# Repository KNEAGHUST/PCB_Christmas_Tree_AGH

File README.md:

<h2>🧐 Features</h2>

So... it's a christmas tree... just made from a PCB!

It is green, has stars on it and... it blinks!

<h2>💾 PCB Design</h2>

The schematics and PCB were designed using KiCAD 7. All the files are available in this repository.

The christmass tree is actually made up of two PCB, that slide into each other and you can solder them toghether.

<h2>💻 Built with</h2>

Technologies used in the project:

*  Microchips Attiny402 microcontroller
*  0805 LEDs and resistors
*  CR2032 battery
*  6 mm tact switch for changing blink modes

<h2>📖 Documentation and project files </h2>

The CTree submodule contains all the code for the attiny, feel free to create pull requests with your own improvements!

KiCAD files has all the schematics and pcb files you might need, but if you just want to build one without making any changes,
Manufacturing files folder has all the gerber files you will need.

Under Materials you should find the current BOM and any oher useful files.

UPDIProgrammer is a python script used to flash the Attiny microcontrolller.

<h2>🛡️ License:</h2>

This project is licensed under the MIT License.

<h2> 🙋‍♂️Authors </h2>

- Krzysztof Sikora (hardware)
- Marek Pawłowski (firmware)

<h2>💖Like my work?</h2>

If you have any questions about the project feel free to contact us via email: krzysieksikora717@gmail.com

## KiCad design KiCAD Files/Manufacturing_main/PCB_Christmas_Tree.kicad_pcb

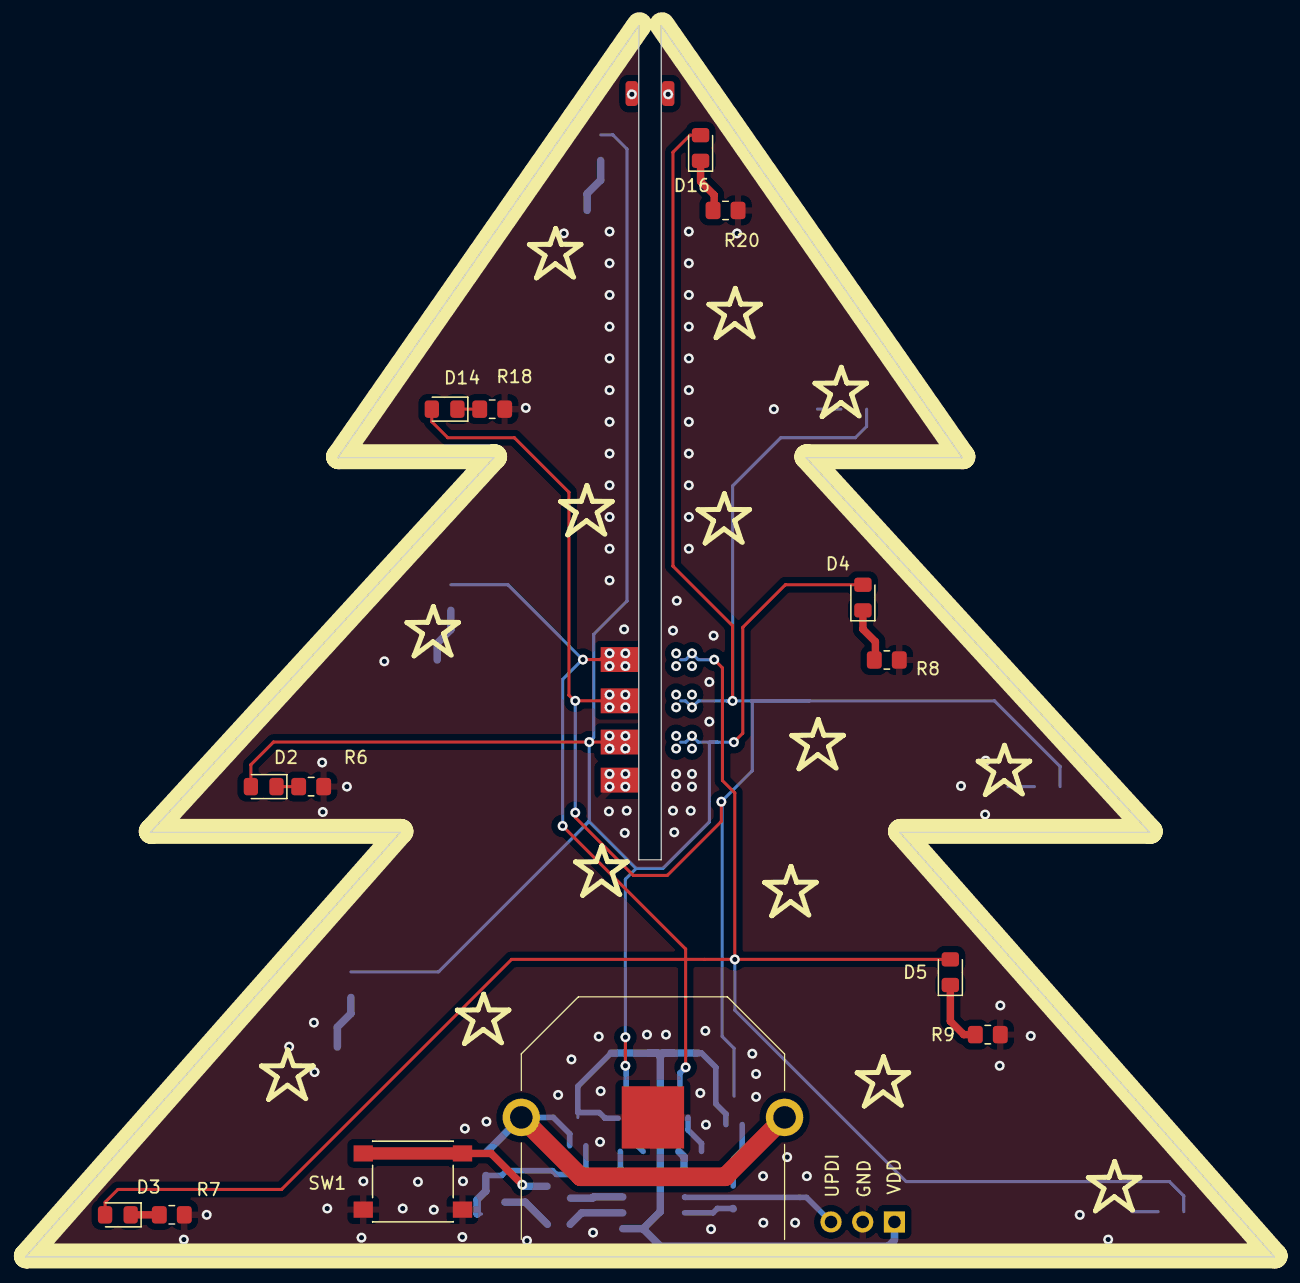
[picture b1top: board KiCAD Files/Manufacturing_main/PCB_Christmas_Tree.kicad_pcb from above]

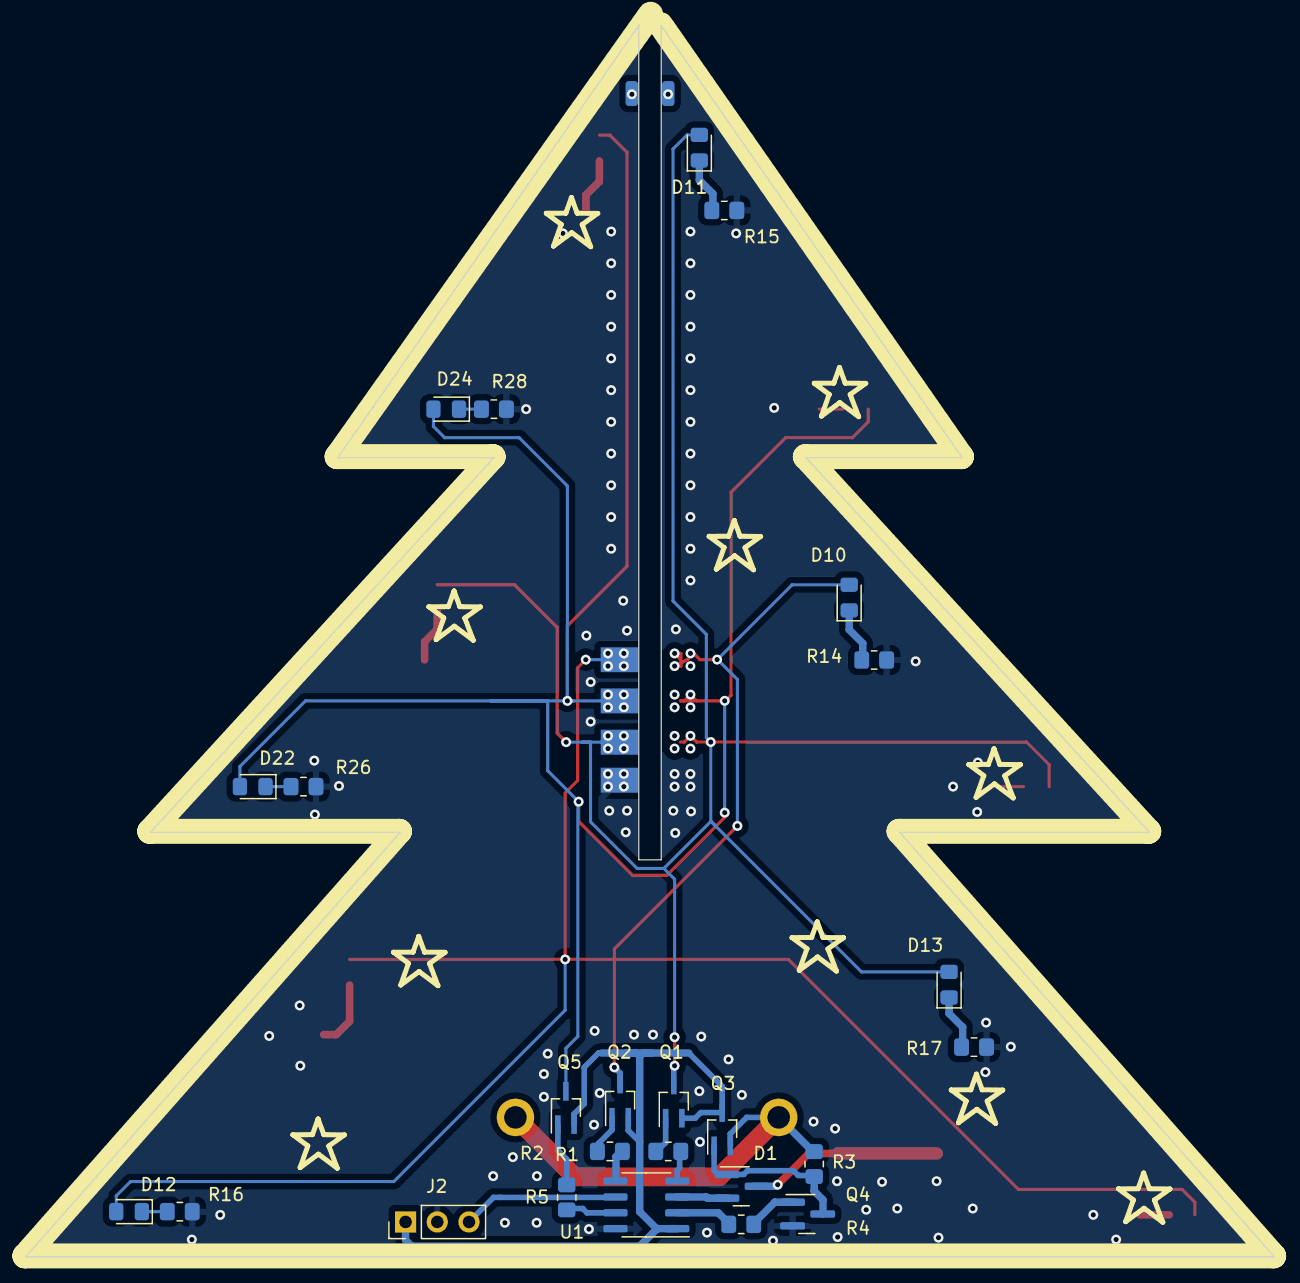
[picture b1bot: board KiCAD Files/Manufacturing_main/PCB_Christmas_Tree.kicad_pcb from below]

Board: 2 copper layers, 100.0 x 98.6 mm, 41 parts (26 on the bottom side), 21 nets.

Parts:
D1: D_Schottky_Dual_CommonCathode_AAK; SOT-23
D2, D3, D4, D5, D10, D11, D12, D13, D14, D16, D22, D24: LED; LED_0805_2012Metric_Pad1.15x1.40mm_HandSolder
J1: CR2032; BC-2002
J2: Conn_01x03_Pin; PinHeader_1x03_P2.54mm_Vertical
J3, J6: Conn_01x04_Pin; Multi_board_connector
Q1, Q2, Q3, Q5: AO3401A; SOT-323_SC-70_Handsoldering
Q4: BC817; SOT-23
R1, R2, R3, R4, R5: 10k; R_0805_2012Metric_Pad1.20x1.40mm_HandSolder
R6, R7, R8, R9, R14, R15, R16, R17, R18, R20, R26, R28: 100; R_0805_2012Metric_Pad1.20x1.40mm_HandSolder
SW1: SW_Omron_B3FS; SW_Push_1P1T_NO_6x6mm_H9.5mm
U1: ATtiny402-SS; SOIC-8_3.9x4.9mm_P1.27mm

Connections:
+BATT: J1.1, Q3.2 (S), R3.1
/LED_Power_1: D3.2 (A), D5.2 (A), D10.2 (A), D12.2 (A), J3.1, J6.1, Q2.3 (D)
/LED_Power_2: D14.2 (A), D16.2 (A), D22.2 (A), D24.2 (A), J3.2, J6.2, Q5.3 (D)
/LED_Power_3: D2.2 (A), D4.2 (A), D11.2 (A), D13.2 (A), J3.3, J6.3, Q1.3 (D)
/LED_Set_1: R2.1, U1.5 (PA2)
/LED_Set_2: R5.1, U1.7 (PA3)
/LED_Set_3: R1.1, U1.4 (PA1)
/Power_sustain: R4.2, U1.2 (PA6)
/Switch_in: D1.2 (A), U1.3 (PA7)
/UDPI: J2.3, U1.6 (~RESET/PA0)
GND: J1.2, J2.2, J3.4, J6.4, Q4.2 (E), R6.2, R7.2, R8.2, R9.2, R14.2, R15.2, R16.2, R17.2, R18.2, R20.2, R26.2, R28.2, SW1.1, U1.8 (GND)
unnamed: D1.3 (K), SW1.2
unnamed: D10.1 (K), R14.1
unnamed: D12.1 (K), R16.1
unnamed: D22.1 (K), R26.1
unnamed: Q1.1 (G), R1.2
unnamed: Q2.1 (G), R2.2
unnamed: D1.1 (A), Q3.1 (G), Q4.3 (C), R3.2
unnamed: Q4.1 (B), R4.1
unnamed: Q5.1 (G), R5.2
VDD: J2.1, Q1.2 (S), Q2.2 (S), Q3.3 (D), Q5.2 (S), U1.1 (VCC)

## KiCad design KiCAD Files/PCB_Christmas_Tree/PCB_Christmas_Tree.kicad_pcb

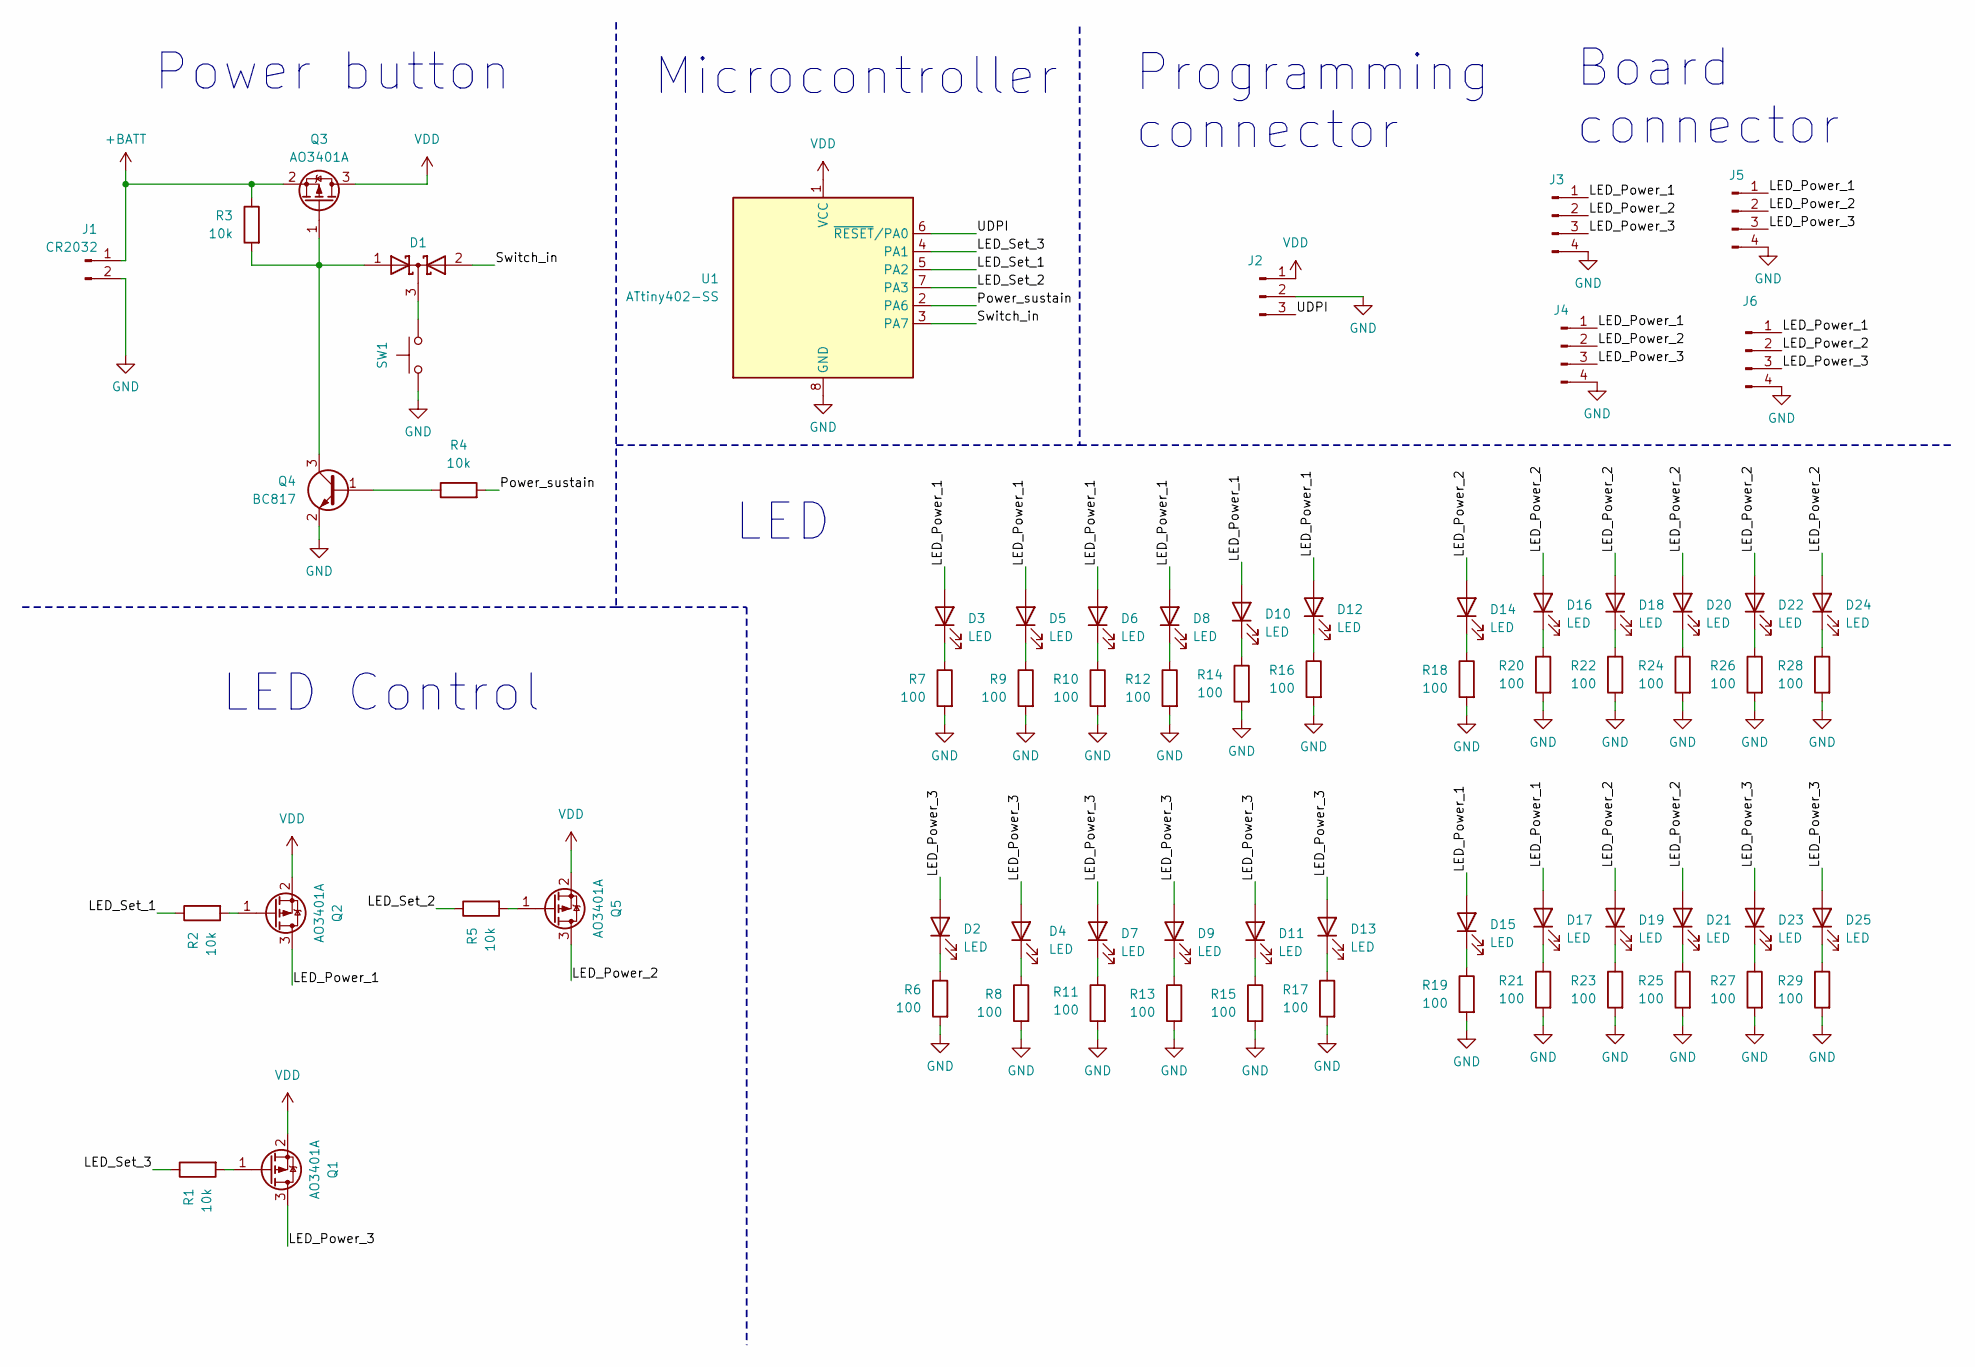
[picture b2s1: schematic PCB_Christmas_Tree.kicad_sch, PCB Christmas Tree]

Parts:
D1: D_Schottky_Dual_CommonCathode_AAK; SOT-23
D2, D3, D4, D5, D6, D7, D8, D9, D10, D11, D12, D13, D14, D15, D16, D17, D18, D19, D20, D21, D22, D23, D24, D25: LED; LED_0805_2012Metric_Pad1.15x1.40mm_HandSolder
J1: CR2032; BC-2002
J2: Conn_01x03_Pin; PinHeader_1x03_P2.54mm_Vertical
J3, J4, J5, J6: Conn_01x04_Pin; Multi_board_connector
Q1, Q2, Q3, Q5: AO3401A; SOT-323_SC-70_Handsoldering
Q4: BC817; SOT-23
R1, R2, R3, R4, R5: 10k; R_0805_2012Metric_Pad1.20x1.40mm_HandSolder
R6, R7, R8, R9, R10, R11, R12, R13, R14, R15, R16, R17, R18, R19, R20, R21, R22, R23, R24, R25, R26, R27, R28, R29: 100; R_0805_2012Metric_Pad1.20x1.40mm_HandSolder
SW1: SW_Omron_B3FS; SW_Push_1P1T_NO_6x6mm_H9.5mm
U1: ATtiny402-SS; SOIC-8_3.9x4.9mm_P1.27mm

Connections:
+BATT: J1.1, Q3.2 (S), R3.1
/LED_Power_1: D3.2 (A), D5.2 (A), D6.2 (A), D8.2 (A), D10.2 (A), D12.2 (A), D15.2 (A), D17.2 (A), J3.1, J4.1, J5.1, J6.1, Q2.3 (D)
/LED_Power_2: D14.2 (A), D16.2 (A), D18.2 (A), D19.2 (A), D20.2 (A), D21.2 (A), D22.2 (A), D24.2 (A), J3.2, J4.2, J5.2, J6.2, Q5.3 (D)
/LED_Power_3: D2.2 (A), D4.2 (A), D7.2 (A), D9.2 (A), D11.2 (A), D13.2 (A), D23.2 (A), D25.2 (A), J3.3, J4.3, J5.3, J6.3, Q1.3 (D)
/LED_Set_1: R2.1, U1.5 (PA2)
/LED_Set_2: R5.1, U1.7 (PA3)
/LED_Set_3: R1.1, U1.4 (PA1)
/Power_sustain: R4.2, U1.2 (PA6)
/Switch_in: D1.2 (A), U1.3 (PA7)
/UDPI: J2.3, U1.6 (~RESET/PA0)
GND: J1.2, J2.2, J3.4, J4.4, J5.4, J6.4, Q4.2 (E), R6.2, R7.2, R8.2, R9.2, R10.2, R11.2, R12.2, R13.2, R14.2, R15.2, R16.2, R17.2, R18.2, R19.2, R20.2, R21.2, R22.2, R23.2, R24.2, R25.2, R26.2, R27.2, R28.2, R29.2, SW1.1, U1.8 (GND)
unnamed: D1.3 (K), SW1.2
unnamed: D2.1 (K), R6.1
unnamed: D3.1 (K), R7.1
unnamed: D4.1 (K), R8.1
unnamed: D5.1 (K), R9.1
unnamed: D6.1 (K), R10.1
unnamed: D7.1 (K), R11.1
unnamed: D8.1 (K), R12.1
unnamed: D9.1 (K), R13.1
unnamed: D10.1 (K), R14.1
unnamed: D11.1 (K), R15.1
unnamed: D12.1 (K), R16.1
unnamed: D13.1 (K), R17.1
unnamed: D14.1 (K), R18.1
unnamed: D15.1 (K), R19.1
unnamed: D16.1 (K), R20.1
unnamed: D17.1 (K), R21.1
unnamed: D18.1 (K), R22.1
unnamed: D19.1 (K), R23.1
unnamed: D20.1 (K), R24.1
unnamed: D21.1 (K), R25.1
unnamed: D22.1 (K), R26.1
unnamed: D23.1 (K), R27.1
unnamed: D24.1 (K), R28.1
unnamed: D25.1 (K), R29.1
unnamed: Q1.1 (G), R1.2
unnamed: Q2.1 (G), R2.2
unnamed: D1.1 (A), Q3.1 (G), Q4.3 (C), R3.2
unnamed: Q4.1 (B), R4.1
unnamed: Q5.1 (G), R5.2
VDD: J2.1, Q1.2 (S), Q2.2 (S), Q3.3 (D), Q5.2 (S), U1.1 (VCC)

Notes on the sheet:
LED
Board connector
LED Control
Power button
Microcontroller
Programming connector

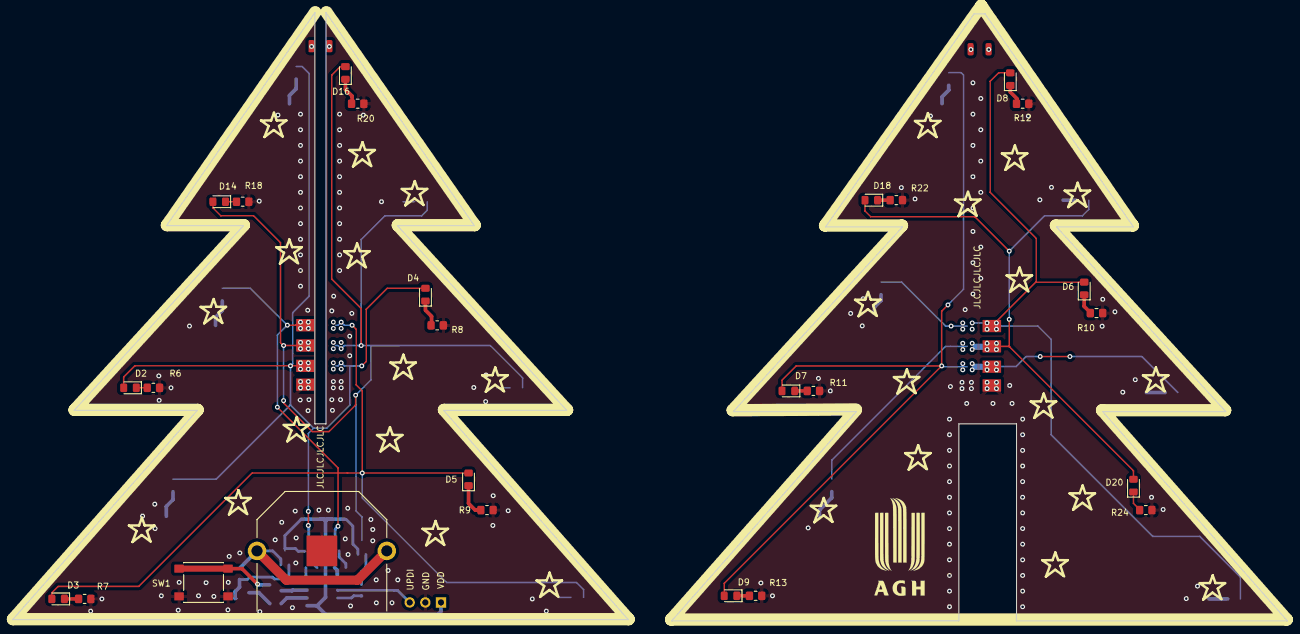
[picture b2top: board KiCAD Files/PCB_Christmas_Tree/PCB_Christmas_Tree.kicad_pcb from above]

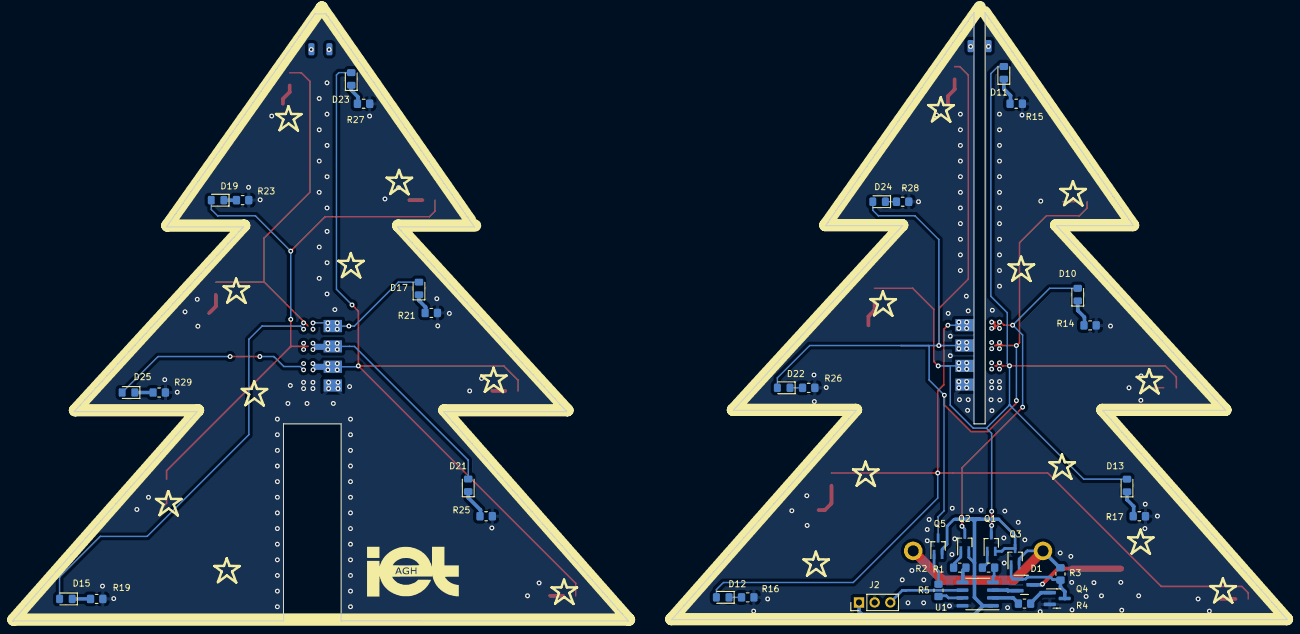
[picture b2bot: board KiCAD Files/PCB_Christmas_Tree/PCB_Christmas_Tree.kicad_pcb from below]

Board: 2 copper layers, 207.1 x 98.8 mm, 67 parts (39 on the bottom side), 42 nets.

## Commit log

2024-03-09 first BOM
2024-03-09 KiCAD project
2024-03-09 schematic revision
2024-03-10 pcb revision
2024-03-10 pcb update
2024-03-10 kicad preparation for production
2024-03-10 gerbers v1
2024-05-26 schematic update, footprint revision
2024-05-26 pcb updates
2024-05-27 pcb modifications
2024-05-27 backup
2024-06-18 v2 added
2024-09-03 add firmware submodule
2024-10-06 kosztorys update
2024-10-06 dodano przelotki
2024-10-08 zmiana pinoutu zlacza UPDI
2024-10-11 Dodano pliki gerber v1
2024-10-12 dodano gerbery bez napisu JLCJLCJLC
2024-11-07 Update CTree
2024-11-13 dodano skrypt do programowania poprzez UPDI
2024-11-13 poprawka do programatora updi
2025-01-18 updated readme, added images
